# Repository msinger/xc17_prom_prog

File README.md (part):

XC17xxx PROM Programmer
=======================

Tool for programming Xilinx XC17xxx families of PROM chips that are used for storing the configuration
bitstream of the Spartan FPGA.

I developed this programmer to be able to program the PROM chips used in the Wide-Boy64. The Wide-Boy64
CGB uses the XC1701L, and the [Wide-Boy64 AGB](http://iceboy.a-singer.de/doc/wide_boy.html) uses the XC17S20XL.

I originally thought that the Wide-Boy64 CGB uses the XC1701 chip (without the L at the end), because that's
how those chips are labeled on their package. After buying some of those XC1701 chips and reading out their
device ID, I realized that they actually are XC1701L chips. This makes sense by the way, since the Spartan
XC4010XL FPGA inside the Wide-Boy64 CGB has 3.3&nbsp;V IO voltage, which matches the XC1701L PROM. The XC1701
is a 5&nbsp;V device.

You can still buy the XC17S20XL chips here:
- https://de.aliexpress.com/item/1005006854844265.html
- https://www.win-source.net/products/detail/xilinx-inc/xc17s20lpc.html
- https://www.win-source.net/products/detail/xilinx-inc/xc17s20xlpd8c.html

You can still buy a very limited supply of the XC1701L chips here:
- https://www.win-source.net/products/detail/xilinx-inc/xc1701pd8c.html

The Xilinx datasheets recommend the XC17512L to be used with the Spartan XC4010XL (which is the FPGA used in
the Wide-Boy64 CGB). So, the XC17512L could be used instead of the XC1701L.

Files in this repo
------------------

| File/Folder                                 | Description                                                            |
| ------------------------------------------- | ---------------------------------------------------------------------- |
| ./pcb/xc17\_prom\_prog/                     | KiCad project.                                                         |
| ./pcb/xc17\_prom\_prog/bom.ods              | Bill of materials (BOM) needed to populate the PCB.                    |
| ./pcb/lib/                                  | KiCad symbol libraries used in KiCad project.                          |
| ./ftdi/xc17\_prom\_prog\_ftdi\_template.xml | Template for configuring the FTDI chip on the PCB.                     |
| ./hdl/                                      | Verilog project that generates the configuration for the iCE40 FPGA.   |
| ./csharp/                                   | C# project that builds the command line tool for using the programmer. |

List of supported chips
-----------------------

I designed the programmer to be able to program the chips listed in the table below. Those are the ones I was able
to find the "Programmer Qualification Specification" datasheets for. Maybe it can be modified to work for other
variants of those PROM chips when more datasheets are found.

| PROM type              | ID   | Voltage group | Word size (bit) | Density (bit) | N<sub>IDCLK</sub> | N<sub>RSTCLK</sub> | T<sub>PGM</sub> (&micro;s) | T<sub>PGM1</sub> (&micro;s) | T<sub>PRST</sub> (&micro;s) |
| :--------------------- | :--- | :-----------: | --------------: | ------------: | ----------------: | -----------------: | -------------------------: | --------------------------: | --------------------------: |
| XC1736E                | 0xED | A             |              32 |         36288 |              2056 |               2048 |                       1000 |                         N/A |                        5000 |
| XC1765E                | 0xFD | A             |              32 |         65536 |              2056 |               2048 |                       1000 |                         N/A |                        5000 |
| XC1765X aka XC1765EL   | 0xFC | B             |              32 |         65536 |              2056 |               2048 |                       1000 |                         N/A |                        5000 |
| XC17128E               | 0x8D | A             |              64 |        131072 |              4600 |               4104 |                       1000 |                         N/A |                        5000 |
| XC17128X aka XC17128EL | 0x8C | B             |              64 |        131072 |              4600 |               4104 |                       1000 |                         N/A |                        5000 |
| XC17256E               | 0xAD | A             |              64 |        262144 |              4600 |               4104 |                       1000 |                         N/A |                        5000 |
| XC17256X aka XC17256EL | 0xAC | B             |              64 |        262144 |              4600 |               4104 |                       1000 |                         N/A |                        5000 |
| XC17S05                | 0xF8 | A             |              32 |         65536 |              2056 |               2048 |                        100 |                         500 |                        5000 |
| XC17S05XL              | 0x87 | B             |              64 |        131072 |              4600 |               4104 |                        100 |                         500 |                        5000 |
| XC17S10                | 0x88 | A             |              64 |        131072 |              4600 |               4104 |                        100 |                         500 |                        5000 |
| XC17S10XL              | 0x89 | B             |              64 |        131072 |              4600 |               4104 |                        100 |                         500 |                        5000 |
| XC17S20                | 0xA8 | A             |              64 |        262144 |              4600 |               4104 |                        100 |                         500 |                        5000 |
| XC17S20XL              | 0xA9 | B             |              64 |        262144 |              4600 |               4104 |                        100 |                         500 |                        5000 |
| XC17S30                | 0xA6 | A             |              64 |        262144 |              4600 |               4104 |                        100 |                         500 |                        5000 |
| XC17S30XL              | 0xA7 | B             |              64 |        262144 |              4600 |               4104 |                        100 |                         500 |                        5000 |
| XC17S40                | 0x98 | A             |              64 |        524288 |             19791 |              16384 |                        100 |                         500 |                        5000 |
| XC17S40XL              | 0x99 | B             |              64 |        524288 |             19791 |              16384 |                        100 |                         500 |                        5000 |
| XC17S50XL              | 0xD6 | B             |              64 |       1048576 |             19791 |              16384 |                        100 |                         500 |                        5000 |
| XC17S100XL             | 0xD7 | B             |              64 |       1048576 |             19791 |              16384 |                        100 |                         500 |                        5000 |
| XC17S150XL             | 0xD9 | B             |              64 |       1048576 |             19791 |              16384 |                        100 |                         500 |                        5000 |
| XC17512L               | 0x9B | B             |              64 |        524288 |             19791 |              16384 |                        100 |                         500 |                        5000 |
| XC1701                 | 0xDA | A             |              64 |       1048576 |             19791 |              16384 |                        100 |                         500 |                        5000 |
| XC1701L                | 0xDB | B             |              64 |       1048576 |             19791 |              16384 |                        100 |                         500 |                        5000 |
| XC1702L                | 0x3B | C             |              64 |       2097152 |             65632 |              65536 |                        100 |                         200 |                         400 |
| XC1704L                | 0xBB | C             |              64 |       4194304 |             65632 |              65536 |                        100 |                         200 |                         400 |

The table also contains the properties that are different between the PROM types. I listed them here to have an overview;
makes it easier than reading through the datasheets over and over.

The ID column contains the device ID, which has the "density code" in its high nibble and the "algorithm code" in the
low nibble.

N<sub>IDCLK</sub> is the number of times the word address needs to be incremented to reach the manufacturer and device ID
page. N<sub>RSTCLK</sub> is the number of times the word address needs to be incremented to reach the page that stores
the reset polarity.

T<sub>PGM</sub> is the time for how long V<sub>PP1</sub> needs to be applied to program a word. T<sub>PGM1</sub> is the
time that V<sub>PP1</sub> needs to be applied for retries when programming failed. Not all PROM types support alternating
programming and verifying on a word for word basis, so not all of them can do retries. T<sub>PRST</sub> is the time for
how long V<sub>PP1</sub> needs to be applied to program the reset polarity.

The PROMs can be divided into three different "voltage groups", which define what voltages need to be applied to the
VCC and VPP pins:

| Group | V<sub>CC</sub>, V<sub>PP</sub>, V<sub>CCVFY</sub> | V<sub>CCP</sub>, V<sub>CCNOM</sub>, V<sub>PPNOM</sub> | V<sub>PP1</sub> | V<sub>PP2</sub> | V<sub>PPVFY</sub> |
| :---: | ------------------------------------------------: | ----------------------------------------------------: | --------------: | --------------: | ----------------: |
| A     |                                          5&nbsp;V |                                              5&nbsp;V |    12.25&nbsp;V |      5.4&nbsp;V |        5.4&nbsp;V |
| B     |                                        3.3&nbsp;V |                                              5&nbsp;V |    12.25&nbsp;V |      5.4&nbsp;V |        3.7&nbsp;V |
| C     |                                        3.3&nbsp;V |                                            3.3&nbsp;V |    12.25&nbsp;V |      3.7&nbsp;V |        3.7&nbsp;V |

PCB Specification
-----------------

I would recommend using the ZIP file from the latest github release, which contains the Gerber and drill files. Use these
parameters for ordering the PCB:

| Parameter         | Value                      |
| ----------------- | -------------------------- |
| Size              | 123&nbsp;x&nbsp;95&nbsp;mm |
| Layers            | 2                          |
| Min hole size     | 0.3&nbsp;mm                |
| Min track/spacing | 6/6&nbsp;mil               |
| Surface finish    | ENIG                       |

The PCB doesn't contain any vias in pads.

PCB population
--------------

There are two ways to populate the PCB:
* Fully populated, including FPGA and FTDI.
  - Programmer doesn't require any additional hardware.
* Partially populated, leaving out the parts inside the dotted area.
  - Programmer needs to be plugged into an
    [iCE40-HX8K Breakout Board](https://www.latticesemi.com/Products/DevelopmentBoardsAndKits/iCE40HX8KBreakoutBoard.aspx).
  - The HX8K Breakout Board needs to be connected via USB to the PC.
  - The programmer PCB needs power over the USB port, but no data connection.

There are some parts that aren't easy to solder by hand, so if you want to save yourself some trouble, you can get
an HX8K Breakout Board. You don't need a cable to connect the two. Just solder a pin header (J3) at the bottom side
of the programmer PCB, you can plug it directly into the already soldered pin sockets of the HX8K Breakout Board (J2).

IF YOU FULLY POPULATED THE PCB, DO _**NOT**_ CONNECT IT TO AN HX8K BREAKOUT BOARD.

The [BOM](pcb/xc17_prom_prog/bom.ods) contains the parts required to fully populate the PCB. If you plan to only
partially populate it, make sure you don't order the non-required expensive parts like FPGA, FTDI and the LT3030
regulator.

FTDI configuration
------------------

The FTDI chip needs to be configured correctly, otherwise the FPGA can't be programmed. The FTDI configuration is held
in the small EEPROM chip (U4). It is programmed via USB using the FT\_PROG utility that you can download from the
[FTDI website](https://ftdichip.com/utilities/). FT\_PROG requires Windows. It also works from inside a Windows 10 VM
running on VirtualBox.

Program the [template file](ftdi/xc17_prom_prog_ftdi_template.xml) from this repository into the EEPROM. Make sure the
EEPROM is erased first.

Build FPGA bitstream
--------------------

To build the bitstream for the FPGA, you need the following tools:
* [yosys](https://github.com/YosysHQ/yosys)
* [nextpnr](https://github.com/YosysHQ/nextpnr)
* [icestorm](https://github.com/YosysHQ/icestorm)
* Plus all the standard development tools like gnumake, autoconf, automake, m4

On Fedora, you can use the following command line to install everything:

```
dnf install yosys nextpnr icestorm make autoconf automake m4
```

Inside the `hdl` directory of the repository, run the following commands to build the bitstream for a fully populated
PCB:

```
autoreconf -i
./configure --enable-board=xc17_prom_prog
make
```

If you've partially populated the PCB and connected it to the HX8K Breakout Board, then use the following commands
instead:

```
autoreconf -i
./configure --enable-board=hx8k_brk
make
```

Program FPGA bitstream into Flash
---------------------------------

The FPGA bitstream needs to be programmed into the flash chip on the PCB or HX8K Breakout Board via USB.

On a fully populated PCB, make sure to put the J1 jumpers into the "Program Flash" configuration, which is
horizontal, like it is indicated on the PCB silk print. JP1 has to be bridged as well. If you want to flash the HX8K
Breakout Board, read the documentation for that. Once the jumpers are placed correctly, you don't have to fiddle
with them anymore. Other jumper configurations are only for development, when you want to test a new FPGA
configuration without burning it into the flash. So you could also bridge the jumpers directly with solder or small
wires on the PCB.

If you've built the FPGA bitstream yourself, you can run the following command inside the `hdl` directory to program
the bitstream:

```
make prog
```

If you want to program a prebuilt release that you've downloaded from github, use the following command:

```
iceprog xc17_prom_prog.bin
```

I haven't tried it, but it should also be possible to use the
[Lattice iCEcube2 Software](https://www.latticesemi.com/en/Products/DesignSoftwareAndIP/FPGAandLDS/iCEcube2)
to program either the `asc` file or the `bin` file.

The green LED D2 (labeled CDONE) indicates that the FPGA has successfully loaded the configuration from the
flash into its configuration RAM. So, on a fully populated PCB, this LED should switch on after the flash was
programmed correctly, every time you power up the board (with the correct jumper configuration described above).
The HX8K Breakout Board also has such an LED (D10) near the jumpers.

Build the command line tool
---------------------------

For building the C# command line tool on Linux, you need the Mono framework and the standard tools gnumake, autoconf,
automake and m4.

For building it on Windows, you need the .NET Framework and some POSIX-like environment for building: Either Cygwin or
Msys2. Gnumake, autoconf, automake and m4 need to be installed in that environment. The C# compiler executable (csc.exe)
must also be callable in your build environment. Make sure it is in `$PATH`.

Run the following commands inside the `csharp` directory of the repository to build the command line tool:

```
autoreconf -i
./configure
make
```

If you want, you can install it with `make install`.

Calibration and testing of PCB
------------------------------

After populating the PCB you have to calibrate all the voltages using the trim potentiometers at the top. Just
hold your voltage meter at the test points near the potentiometers. The target voltage that each test point should
have is labeled on the silk screen print.

If the LDOs are not providing high enough voltages, check if the step-up converters provide roughly 15&nbsp;V and
8.5&nbsp;V at test points TP12 and TP13. The 15&nbsp;V is used by the first LDO (U6) to generate the 12.25&nbsp;V.
The other six LDOs use the 8.5&nbsp;V to generate their lower voltages. In case you are wondering, the reason why
there are two 3.3&nbsp;V LDOs and two 5&nbsp;V LDOs is this: One of each is there for providing the VCC voltage for
the PROM, the other one (of each) is there for providing the VPP voltage. We can't use the same LDOs for VCC and
VPP, because VPP will be switched to 12.25&nbsp;V for issuing the programming pulses. There is a short moment during
switching where the 12.25&nbsp;V and the lower voltage (3.3&nbsp;V or 5&nbsp;V) will both be connected to VPP at the
same time. At this moment, the 12.25&nbsp;V will back flow to the other LDO. If we'd use the same LDO, then the
12.25&nbsp;V would also reach the VCC pin of the PROM, which is not good. VCC needs to be constant at all time, and
it can't handle 12&nbsp;V. Only VPP can switch around.

Before trying to read or program an actual PROM chip, you first should do some tests to make sure the PCB is
working correctly.

Connect the PCB via USB and run the command line tool with the following options:

```
xc17_prom_prog.exe COMMPORT --test-echo
```

Replace *`COMMPORT`* with the correct serial port. On Windows this would be `COM2:` or something. On Linux it is
something like `/dev/ttyUSB1`. The FTDI chip has two serial ports. Usually, the first one is the one that is used
for programming the flash chip (U1) that holds the FPGA bitstream. The second port is the one we need most likely,
so try this one first. Of course, on Linux you have to call the command with `mono`, like this:

```
mono xc17_prom_prog.exe /dev/ttyUSB1 --test-echo
```

`--test-echo` just tests the serial communication and the BRAM inside the FPGA.

Next, we can test the voltage switching MOSFETs:

```
xc17_prom_prog.exe COMMPORT --test-voltage VOLTAGE
```

Again, replace *`COMMPORT`* with the actual port. For *`VOLTAGE`* insert one of the following:

 - `vcc-3v3`
 - `vcc-5v`
 - `vpp-3v3`
 - `vpp-3v7`
 - `vpp-5v`
 - `vpp-5v4`
 - `vpp-12v25`
 - `off`

For example, `vcc-3v3` will switch 3.3&nbsp;V onto the VCC pin of the PROM. (Don't actually put a PROM chip
into the socket when testing the voltages, please!) You can measure that with your voltage meter at test point
TP19. `vpp-5v4` will switch 5.4&nbsp;V onto the VPP pin at test point TP18, and so on. This test option only
enables one single voltage at a time, so don't worry, you can't make short circuits. `off` switches all MOSFETs
off, as the name implies. The red LED (D20) signals whenever at least one of the two pins (VCC, VPP) is powered
to indicate that you shouldn't insert or remove the chip right now.

There are actually three other options that can be inserted for *`VOLTAGE`* (`vcc-gnd`, `vpp-gnd` and
`vpp-gnd-weak`), but you can't measure anything there, because they are pulling the respective pin to ground.

If the voltage switching works, we should test if the 12.25&nbsp;V pulse looks okay using an oscilloscope. Hook
up one probe to test point TP18 (VPP<sub>PROM</sub>) and one to TP19 (VCC<sub>PROM</sub>). Configure the trigger
to around ~8&nbsp;V on the probe connected to VPP<sub>PROM</sub>, so we can trigger when VPP raises from
5&nbsp;V to 12.25&nbsp;V. Then run this command:

```
xc17_prom_prog.exe COMMPORT --prom xc17s20xl --detect
```

`--prom xc17s20xl` configures the programmer to use the voltages required by the XC17S20XL PROM chip (which is
used in the Wide-Boy64 AGB). This PROM chip is a 3.3&nbsp;V device, but it needs to be powered with 5&nbsp;V
to enter "programming mode". `--detect` makes the programmer just read the manufacturer and device IDs of the
PROM chip, without reading or programming anything else. For reading the IDs, the PROM has to enter "programming
mode", which sounds counterintuitive, but that's how it's done. So, the programmer will switch VCC and VPP to
5&nbsp;V. Then shortly after switching them to 5&nbsp;V, it will issue a short pulse of 12.25&nbsp;V on VPP.

On the oscilloscope we want to check the following things:

 * There should be no over and/or under shooting when the voltage on VPP raises from 5&nbsp;V to 12.25&nbsp;V
   and falls back down to 5&nbsp;V.
 * The raising and falling of the voltage on VPP shouldn't take much longer than 5&nbsp;&micro;s.
 * According to the datasheets, VCC must stay stable within &plusmn;50&nbsp;mV. I wasn't able to comply with
   that. My VCC was always swinging a bit more when the 12.25&nbsp;V ramps up on VPP. I couldn't figure out
   why this happens and how to fix it. Just make sure VCC looks reasonable, programming the PROM will work
   anyway.

If VPP takes too long to fall down to 5&nbsp;V, then the resistor R82 is probably too big and you should try
a smaller one. If VPP drops below 5&nbsp;V or if it is unstable or oscillating for some microseconds after
falling down, then resistor R82 could be too small. Try a bigger one in that case.

This picture shows VCC (yellow) and VPP (cyan) during the 12.25&nbsp;V pulse. The dark blue and purple channels
are added, so I can correctly photoshop the additional signals from the logic analyzer underneath the
oscilloscope screenshot. You can see VCC getting a bit unstable while VPP rises to 12.25&nbsp;V. There is a
delay of 4&nbsp;&micro;s between switching off the 5&nbsp;V LDO and switching on the 12.25&nbsp;V LDO for VPP.
This delay is needed, because when switching off, it takes 2 or 3&nbsp;&micro;s until the gates of the MOSFETs
get drained and the MOSFETs actually switch off. I had chosen a slightly longer delay to make sure that the
5 and 12.25&nbsp;V LDOs are not switched on at the same time, because this would allow the 12.25&nbsp;V to
backflow through the diode (D5) above the 5&nbsp;V LDO. This would destabilize both voltages and takes a long
time for VPP to climb up to 12.25&nbsp;V due to the near short circuit through the diode. The same
4&nbsp;&micro;s pause exists at the end of the pulse, where the 12.25&nbsp;V gets drained by switching on the
VPP\_GND and VPP\_GND\_WEAK signals. VPP\_GND switches on the NPN transistor Q20 to quickly drain VPP down
towards GND. VPP\_GND\_WEAK switches on Q21 to drain VPP through resistor R82. VPP\_GND is only enabled for
2&nbsp;&micro;s. We don't want to drain VPP lower than 5&nbsp;V. We could leave it enabled for longer, but
I want to stay on the safe side, we need to consider tolerances of the BC850 transistors. VPP\_GND\_WEAK is
enabled for 7&nbsp;&micro;s and VPP\_5V (which enables the 5&nbsp;V LDO) overlaps with it for 2&nbsp;&micro;s.
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
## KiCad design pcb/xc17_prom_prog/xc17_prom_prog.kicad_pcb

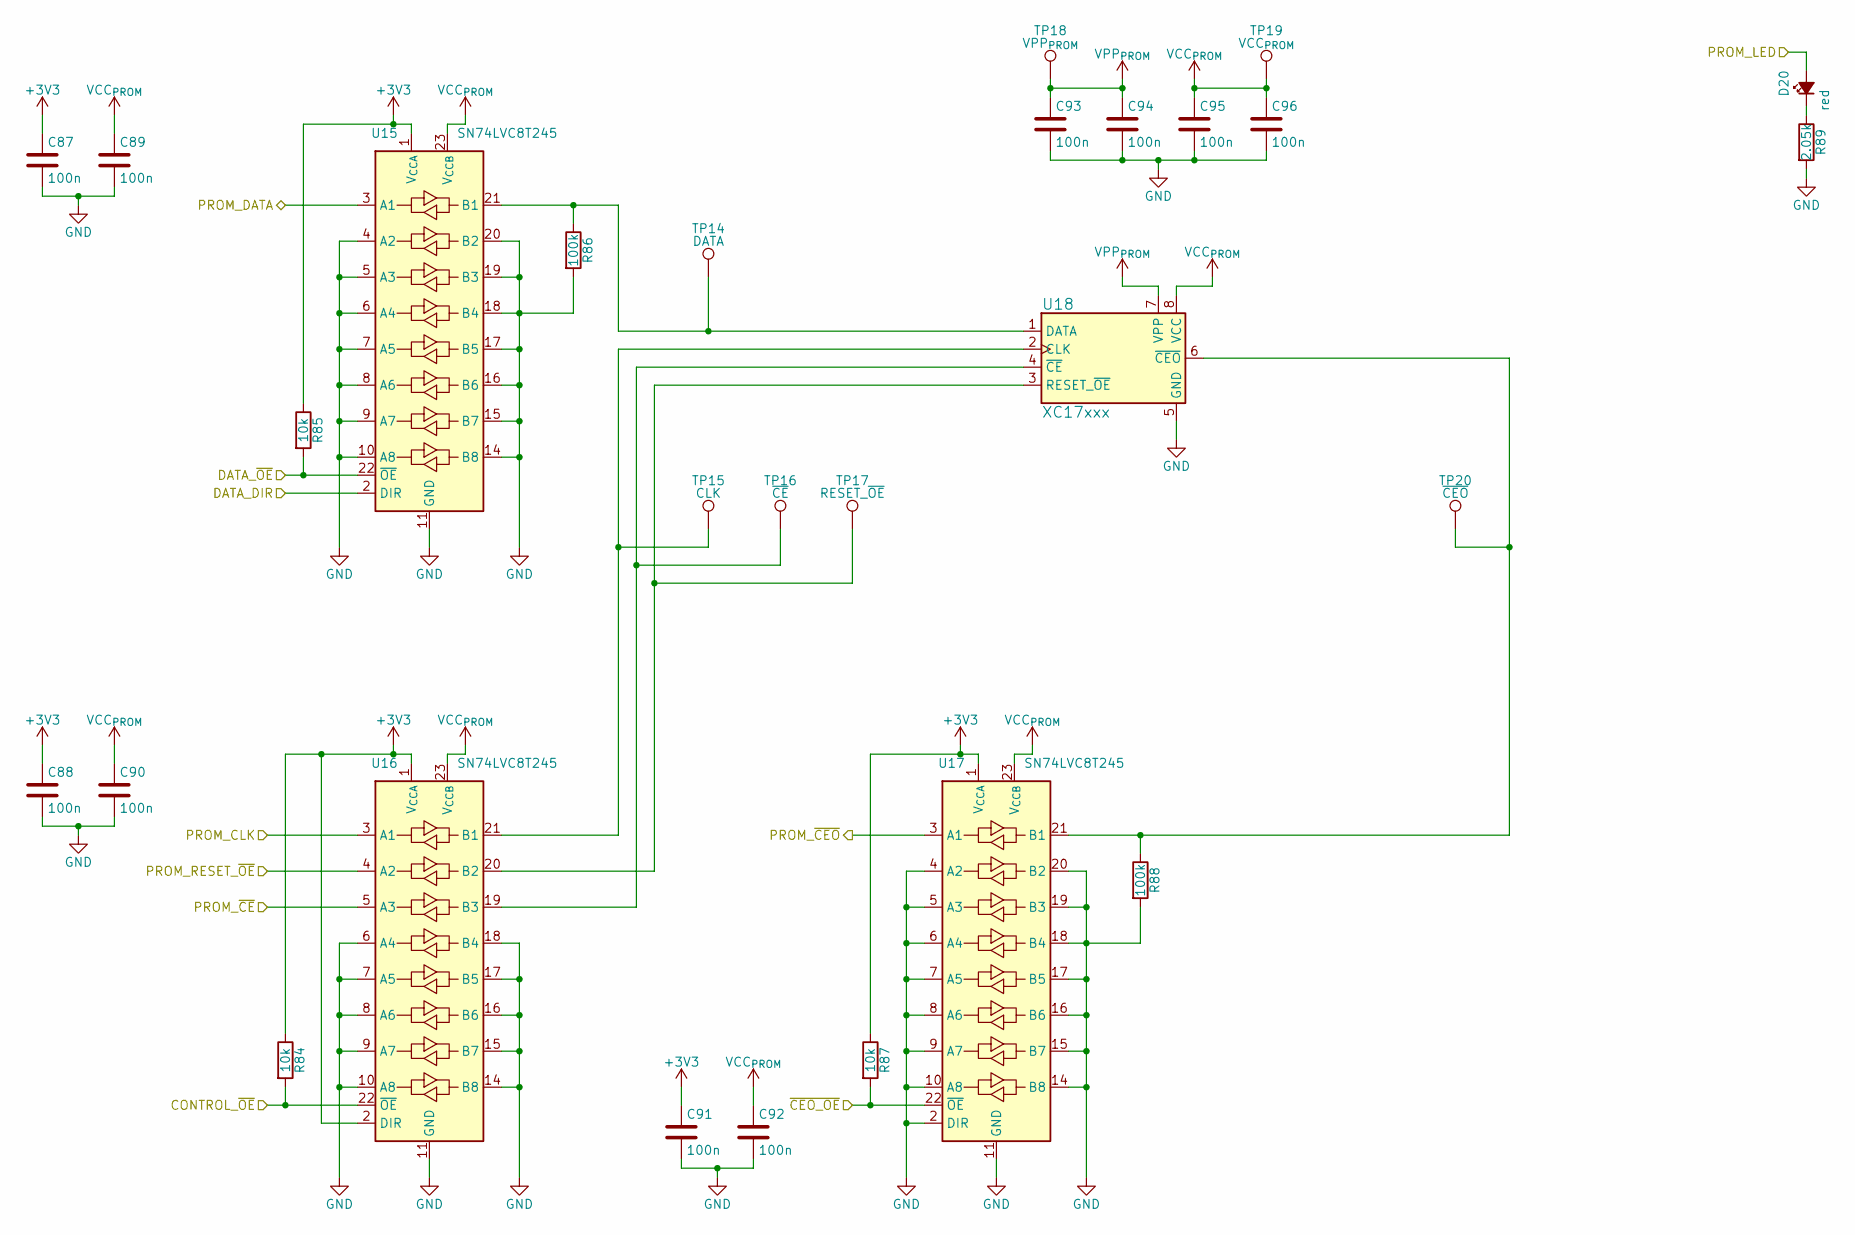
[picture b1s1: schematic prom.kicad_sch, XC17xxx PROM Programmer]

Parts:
C87, C88, C89, C90, C91, C92, C93, C94, C95, C96: 100n; C_0603_1608Metric
D20: red; LED_0805_2012Metric
R84, R85, R87: 10k; R_0603_1608Metric
R86, R88: 100k; R_0603_1608Metric
R89: 2.05k; R_0603_1608Metric
TP14: DATA; TestPoint_Keystone_5010-5014_Multipurpose
TP15: CLK; TestPoint_Keystone_5010-5014_Multipurpose
TP16: ~{CE}; TestPoint_Keystone_5010-5014_Multipurpose
TP17: RESET_~{OE}; TestPoint_Keystone_5010-5014_Multipurpose
TP18: VPP_{PROM}; TestPoint_Keystone_5010-5014_Multipurpose
TP19: VCC_{PROM}; TestPoint_Keystone_5010-5014_Multipurpose
TP20: ~{CEO}; TestPoint_Keystone_5010-5014_Multipurpose
U15, U16, U17: SN74LVC8T245; TSSOP-24_4.4x7.8mm_P0.65mm
U18: XC17xxx; DIP-8_W7.62mm_Socket

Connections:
+3V3: C87.1, C88.1, C91.1, R84.1, R85.1, R87.1, U15.1 (V_{CCA}), U16.1 (V_{CCA}), U16.2 (DIR), U17.1 (V_{CCA}); also elsewhere on the board
/FPGA/CONTROL_~OE: R84.2, U16.22 (~OE); also elsewhere on the board
/FPGA/DATA_DIR: U15.2 (DIR); also elsewhere on the board
/FPGA/DATA_~OE: R85.2, U15.22 (~OE); also elsewhere on the board
/FPGA/PROM_CLK: U16.3 (A1); also elsewhere on the board
/FPGA/PROM_DATA: U15.3 (A1); also elsewhere on the board
/FPGA/PROM_LED: D20.2 (A); also elsewhere on the board
/FPGA/PROM_RESET_~OE: U16.4 (A2); also elsewhere on the board
/FPGA/PROM_~CEO: U17.3 (A1); also elsewhere on the board
/FPGA/PROM_~CE: U16.5 (A3); also elsewhere on the board
/FPGA/~CEO_OE: R87.2, U17.22 (~OE); also elsewhere on the board
GND: C87.2, C88.2, C89.2, C90.2, C91.2, C92.2, C93.2, C94.2, C95.2, C96.2, R86.2, R88.2, R89.2, U15.4 (A2), U15.5 (A3), U15.6 (A4), U15.7 (A5), U15.8 (A6), U15.9 (A7), U15.10 (A8), U15.11 (GND), U15.12 (GND), U15.13 (GND), U15.14 (B8), U15.15 (B7), U15.16 (B6), U15.17 (B5), U15.18 (B4), U15.19 (B3), U15.20 (B2), U16.6 (A4), U16.7 (A5), U16.8 (A6), U16.9 (A7), U16.10 (A8), U16.11 (GND), U16.12 (GND), U16.13 (GND), U16.14 (B8), U16.15 (B7), U16.16 (B6), U16.17 (B5), U16.18 (B4), U17.2 (DIR), U17.4 (A2), U17.5 (A3), U17.6 (A4), U17.7 (A5), U17.8 (A6), U17.9 (A7), U17.10 (A8), U17.11 (GND), U17.12 (GND), U17.13 (GND), U17.14 (B8), U17.15 (B7), U17.16 (B6), U17.17 (B5), U17.18 (B4), U17.19 (B3), U17.20 (B2), U18.5 (GND); also elsewhere on the board
unnamed: D20.1 (K), R89.1
unnamed: R86.1, TP14.1, U15.21 (B1), U18.1 (DATA)
unnamed: TP15.1, U16.21 (B1), U18.2 (CLK)
unnamed: TP17.1, U16.20 (B2), U18.3 (RESET_~OE)
unnamed: TP16.1, U16.19 (B3), U18.4 (~CE)
unnamed: R88.1, TP20.1, U17.21 (B1), U18.6 (~CEO)
VCC_{PROM}: C89.1, C90.1, C92.1, C95.1, C96.1, TP19.1, U15.23 (V_{CCB}), U15.24 (V_{CCB}), U16.23 (V_{CCB}), U16.24 (V_{CCB}), U17.23 (V_{CCB}), U17.24 (V_{CCB}), U18.8 (VCC); also elsewhere on the board
VPP_{PROM}: C93.1, C94.1, TP18.1, U18.7 (VPP); also elsewhere on the board

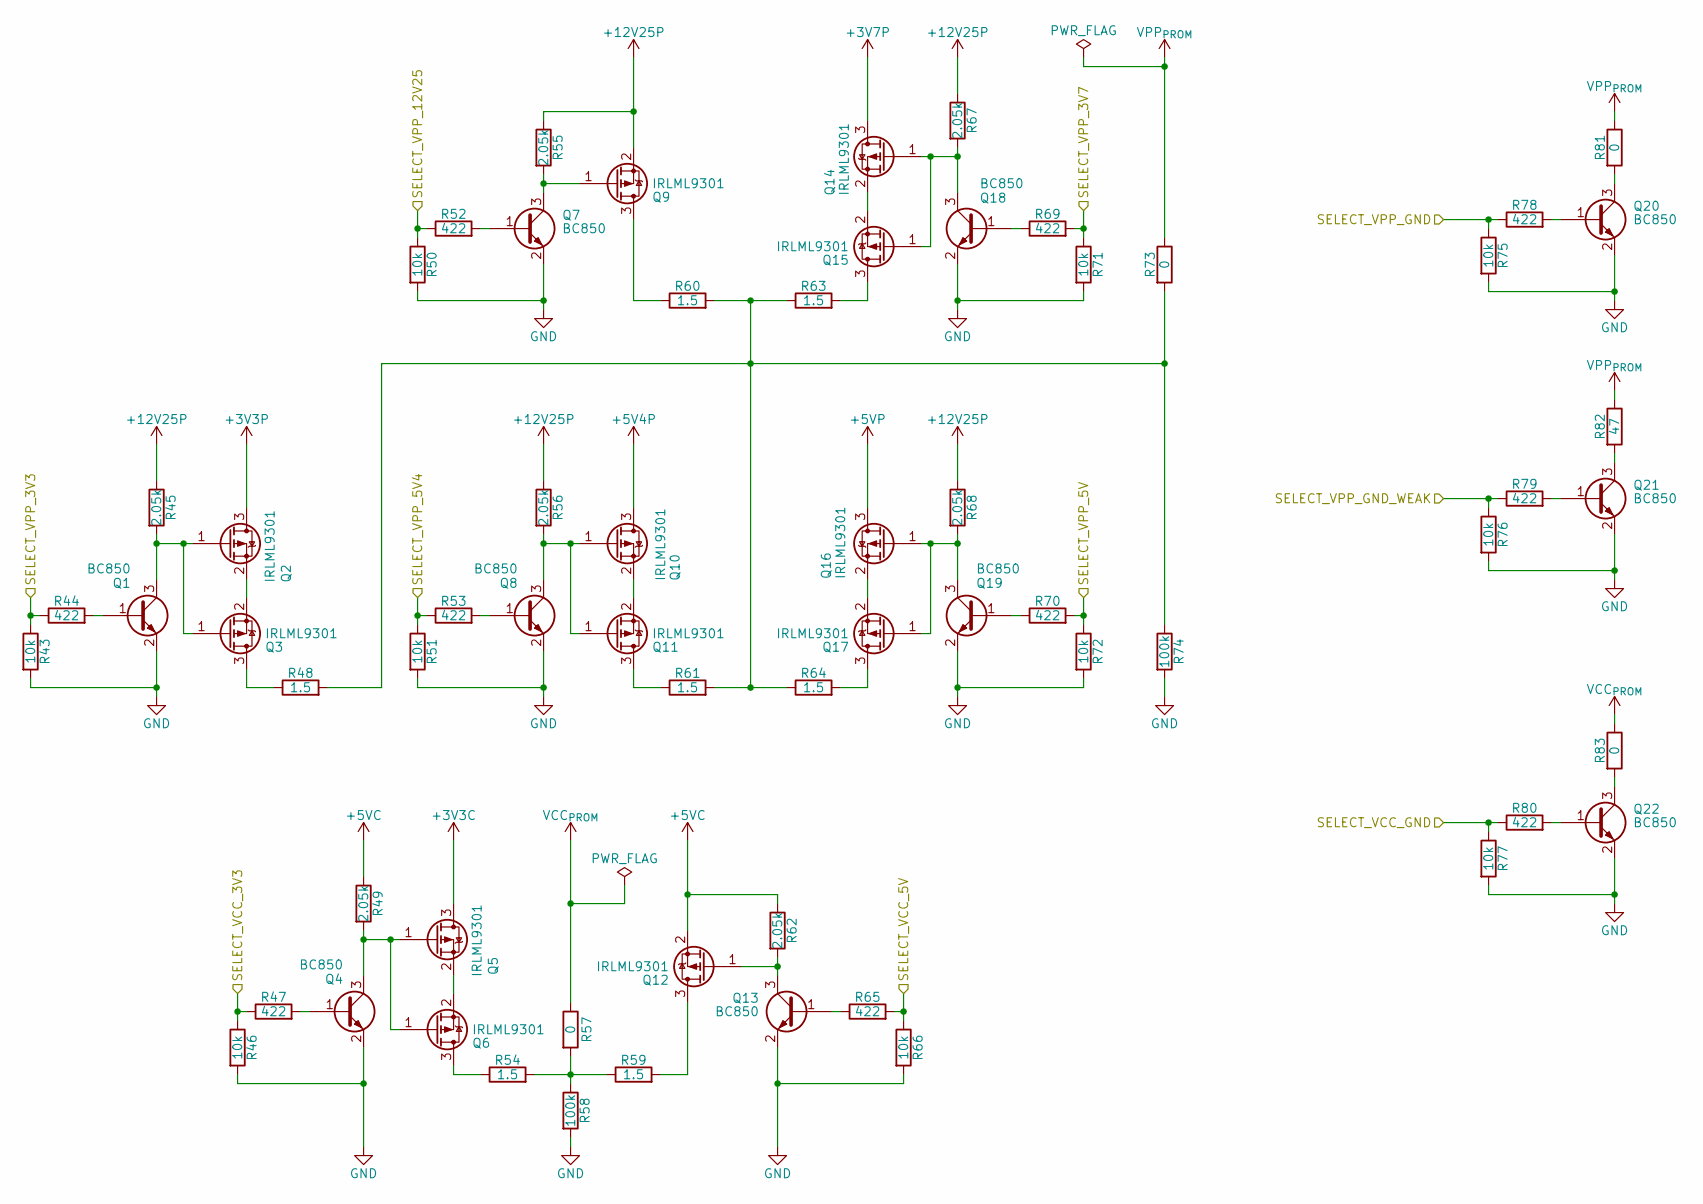
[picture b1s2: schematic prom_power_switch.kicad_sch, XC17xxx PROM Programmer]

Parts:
Q1, Q4, Q7, Q8, Q13, Q18, Q19, Q20, Q21, Q22: BC850; SOT-23
Q2, Q3, Q5, Q6, Q9, Q10, Q11, Q12, Q14, Q15, Q16, Q17: IRLML9301; SOT-23
R43, R46, R50, R51, R66, R71, R72, R75, R76, R77: 10k; R_0603_1608Metric
R44, R47, R52, R53, R65, R69, R70, R78, R79, R80: 422; R_0603_1608Metric
R45, R49, R55, R56, R62, R67, R68: 2.05k; R_0603_1608Metric
R48, R54, R59, R60, R61, R63, R64: 1.5; R_0603_1608Metric
R57, R73, R81, R83: 0; R_0603_1608Metric
R58, R74: 100k; R_0603_1608Metric
R82: 47; R_0603_1608Metric

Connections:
+3V3C: Q5.3 (D); also elsewhere on the board
+3V3P: Q2.3 (D); also elsewhere on the board
+3V7P: Q14.3 (D); also elsewhere on the board
+5V4P: Q10.3 (D); also elsewhere on the board
+5VC: Q12.2 (S), R49.1, R62.1; also elsewhere on the board
+5VP: Q16.3 (D); also elsewhere on the board
+12V25P: Q9.2 (S), R45.1, R55.1, R56.1, R67.1, R68.1; also elsewhere on the board
/FPGA/SELECT_VCC_3V3: R46.1, R47.1; also elsewhere on the board
/FPGA/SELECT_VCC_5V: R65.2, R66.1; also elsewhere on the board
/FPGA/SELECT_VCC_GND: R77.1, R80.1; also elsewhere on the board
/FPGA/SELECT_VPP_3V3: R43.1, R44.1; also elsewhere on the board
/FPGA/SELECT_VPP_3V7: R69.2, R71.1; also elsewhere on the board
/FPGA/SELECT_VPP_5V: R70.2, R72.1; also elsewhere on the board
/FPGA/SELECT_VPP_5V4: R51.1, R53.1; also elsewhere on the board
/FPGA/SELECT_VPP_12V25: R50.1, R52.1; also elsewhere on the board
/FPGA/SELECT_VPP_GND: R75.1, R78.1; also elsewhere on the board
/FPGA/SELECT_VPP_GND_WEAK: R76.1, R79.1; also elsewhere on the board
GND: Q1.2 (E), Q4.2 (E), Q7.2 (E), Q8.2 (E), Q13.2 (E), Q18.2 (E), Q19.2 (E), Q20.2 (E), Q21.2 (E), Q22.2 (E), R43.2, R46.2, R50.2, R51.2, R58.2, R66.2, R71.2, R72.2, R74.2, R75.2, R76.2, R77.2; also elsewhere on the board
unnamed: Q1.1 (B), R44.2
unnamed: Q1.3 (C), Q2.1 (G), Q3.1 (G), R45.2
unnamed: Q2.2 (S), Q3.2 (S)
unnamed: Q3.3 (D), R48.1
unnamed: Q4.1 (B), R47.2
unnamed: Q4.3 (C), Q5.1 (G), Q6.1 (G), R49.2
unnamed: Q5.2 (S), Q6.2 (S)
unnamed: Q6.3 (D), R54.1
unnamed: Q7.1 (B), R52.2
unnamed: Q7.3 (C), Q9.1 (G), R55.2
unnamed: Q8.1 (B), R53.2
unnamed: Q9.3 (D), R60.1
unnamed: Q8.3 (C), Q10.1 (G), Q11.1 (G), R56.2
unnamed: Q10.2 (S), Q11.2 (S)
unnamed: Q11.3 (D), R61.1
unnamed: Q12.3 (D), R59.2
unnamed: Q12.1 (G), Q13.3 (C), R62.2
unnamed: Q13.1 (B), R65.1
unnamed: Q14.1 (G), Q15.1 (G), Q18.3 (C), R67.2
unnamed: Q14.2 (S), Q15.2 (S)
unnamed: Q15.3 (D), R63.2
unnamed: Q16.1 (G), Q17.1 (G), Q19.3 (C), R68.2
unnamed: Q16.2 (S), Q17.2 (S)
unnamed: Q17.3 (D), R64.2
unnamed: Q18.1 (B), R69.1
unnamed: Q19.1 (B), R70.1
unnamed: Q20.1 (B), R78.2
unnamed: Q20.3 (C), R81.2
unnamed: Q21.1 (B), R79.2
unnamed: Q21.3 (C), R82.2
unnamed: Q22.1 (B), R80.2
unnamed: Q22.3 (C), R83.2
unnamed: R48.2, R60.2, R61.2, R63.1, R64.1, R73.2, R74.1
unnamed: R54.2, R57.2, R58.1, R59.1
VCC_{PROM}: R57.1, R83.1; also elsewhere on the board
VPP_{PROM}: R73.1, R81.1, R82.1; also elsewhere on the board

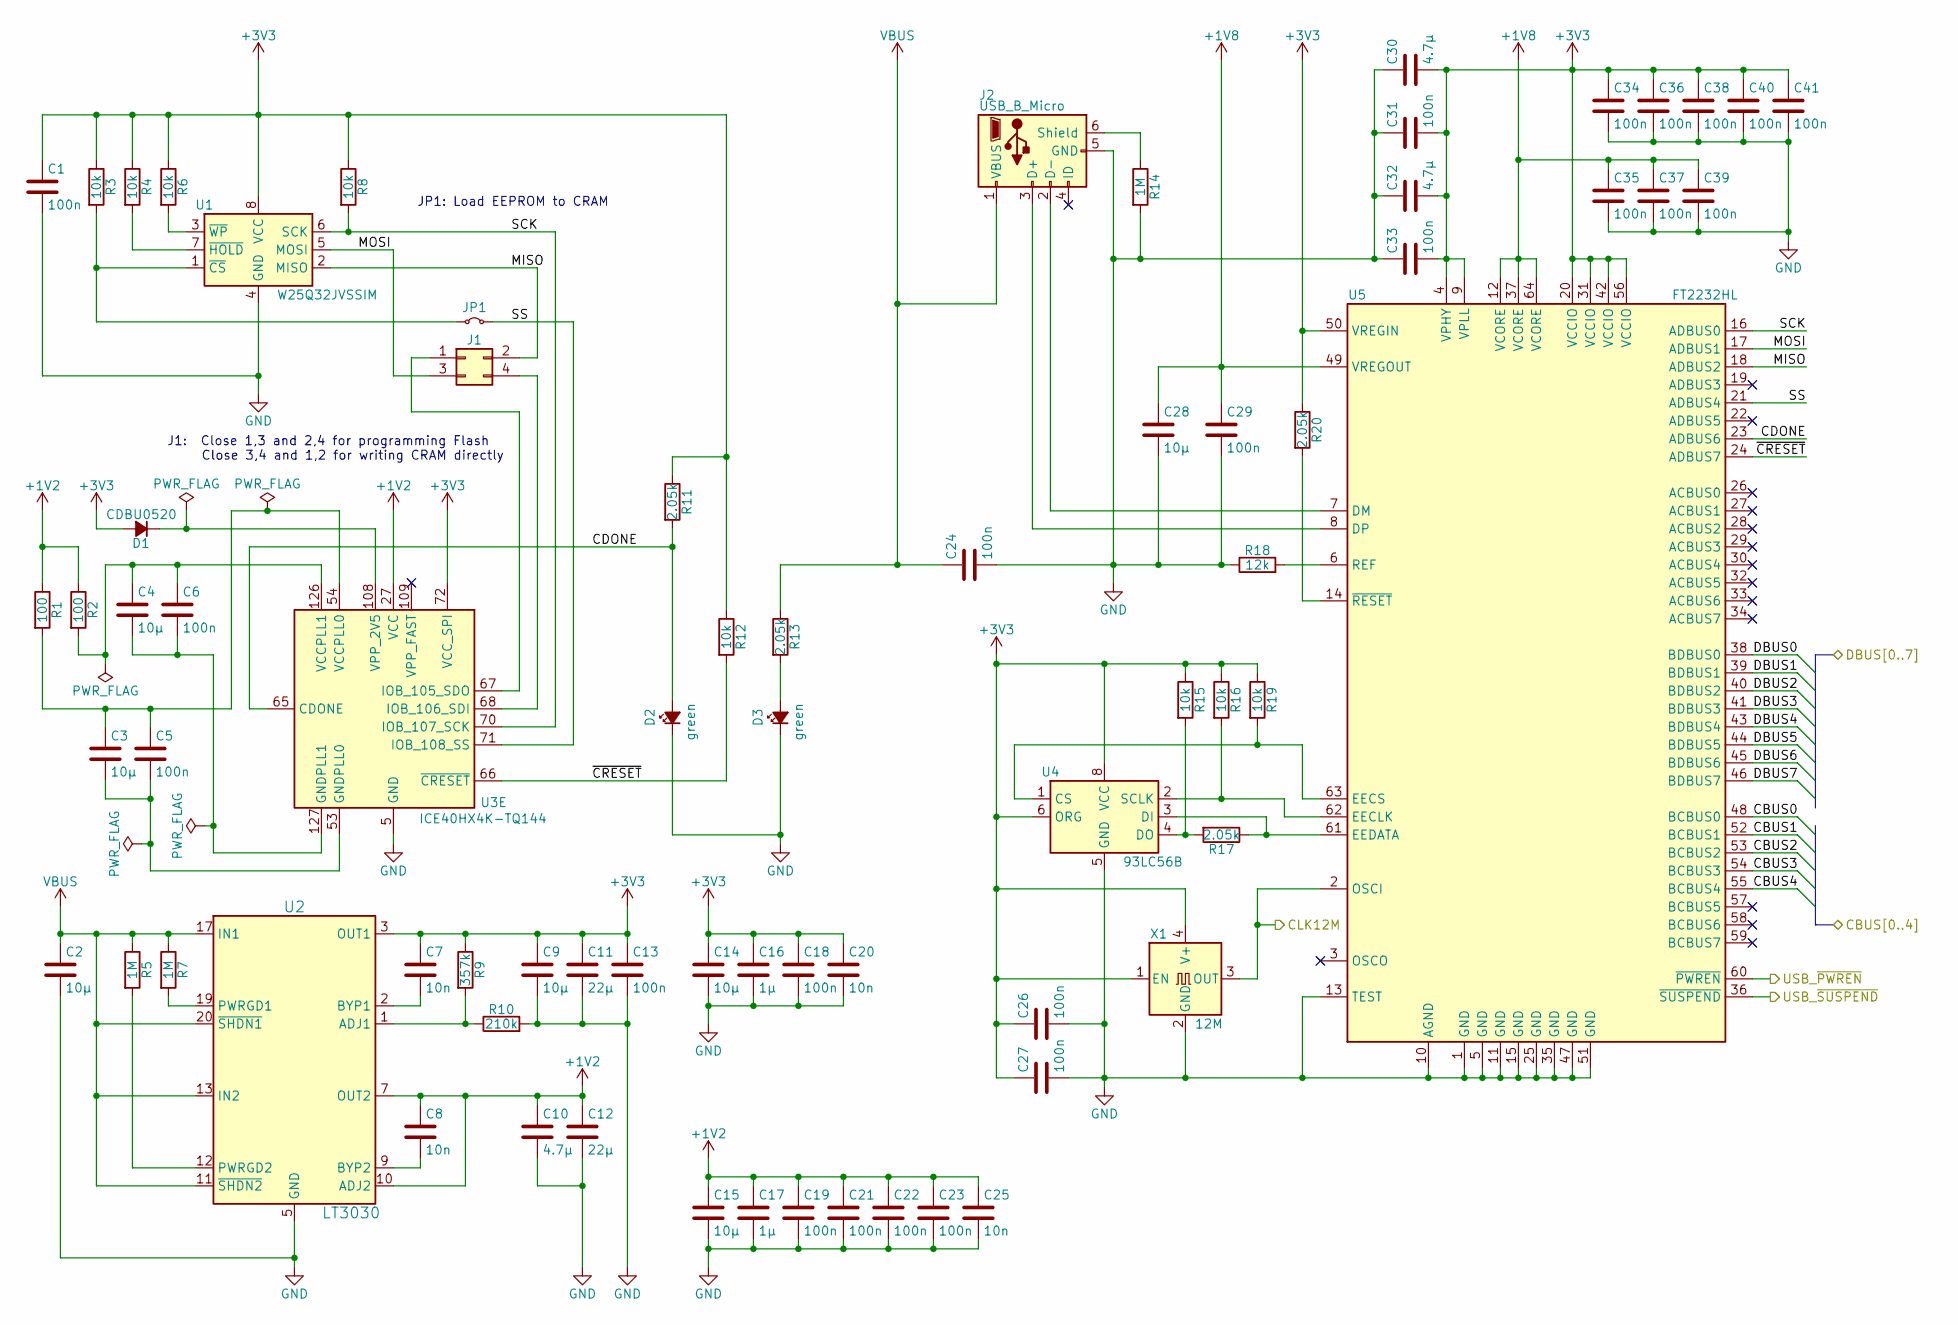
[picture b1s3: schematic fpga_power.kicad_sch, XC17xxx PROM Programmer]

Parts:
C1, C5, C6, C13, C18, C19, C21, C22, C23, C24, C26, C27, C29, C31, C33, C34, C35, C36, C37, C38, C39, C40, C41: 100n; C_0603_1608Metric
C2, C3, C4, C9, C14, C15, C28: 10µ; C_0603_1608Metric
C7, C8, C20, C25: 10n; C_0603_1608Metric
C10, C30, C32: 4.7µ; C_0603_1608Metric
C11, C12: 22µ; C_0805_2012Metric
C16, C17: 1µ; C_0603_1608Metric
D1: CDBU0520; D_0603_1608Metric
D2, D3: green; LED_0805_2012Metric
J1: Conn_02x02_Odd_Even; PinHeader_2x02_P2.54mm_Vertical
J2: USB_B_Micro; USB_Micro-B_Molex-105017-0001
JP1: Jumper_2_Small_Bridged; TestPoint_2Pads_Pitch2.54mm_Drill0.8mm
R1, R2: 100; R_0603_1608Metric
R3, R4, R6, R8, R12, R15, R16, R19: 10k; R_0603_1608Metric
R5, R7, R14: 1M; R_0603_1608Metric
R9: 357k; R_0603_1608Metric
R10: 210k; R_0603_1608Metric
R11, R13, R17, R20: 2.05k; R_0603_1608Metric
R18: 12k; R_0603_1608Metric
U1: W25Q32JVSSIM; SOIC-8W_5.3x5.3mm_P1.27mm
U2: LT3030; ETSSOP-20-1EP_4.4x6.5mm_P0.65mm_EP3x4.2mm
U3: ICE40HX4K-TQ144; TQFP-144_20x20mm_P0.5mm
U4: 93LC56B; SOIC-8_3.9x4.9mm_P1.27mm
U5: FT2232HL; LQFP-64_10x10mm_P0.5mm
X1: 12M; Oscillator_SMD_EuroQuartz_XO32-4Pin_3.2x2.5mm

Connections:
+1V2: C8.1, C10.1, C12.1, C15.1, C17.1, C19.1, C21.1, C22.1, C23.1, C25.1, R1.1, R2.1, U2.7 (OUT2), U2.8 (OUT2), U2.10 (ADJ2), U3.27 (VCC), U3.40 (VCC), U3.92 (VCC), U3.111 (VCC)
+1V8: C28.1, C29.1, C35.1, C37.1, C39.1, U5.12 (VCORE), U5.37 (VCORE), U5.49 (VREGOUT), U5.64 (VCORE)
+3V3: C1.1, C7.1, C9.1, C11.1, C13.1, C14.1, C16.1, C18.1, C20.1, C26.1, C27.1, C30.2, C31.2, C32.2, C33.2, C34.1, C36.1, C38.1, C40.1, C41.1, D1.2 (A), R3.1, R4.1, R6.1, R8.1, R9.1, R11.1, R12.1, R15.1, R16.1, R19.1, R20.1, U1.8 (VCC), U2.3 (OUT1), U2.4 (OUT1), U3.72 (VCC_SPI), U4.6 (ORG), U4.8 (VCC), U5.4 (VPHY), U5.9 (VPLL), U5.20 (VCCIO), U5.31 (VCCIO), U5.42 (VCCIO), U5.50 (VREGIN), U5.56 (VCCIO), X1.1 (EN), X1.4 (V+); also elsewhere on the board
/FPGA Power/CBUS0: U5.48 (BCBUS0); also elsewhere on the board
/FPGA Power/CBUS1: U5.52 (BCBUS1); also elsewhere on the board
/FPGA Power/CBUS2: U5.53 (BCBUS2); also elsewhere on the board
/FPGA Power/CBUS3: U5.54 (BCBUS3); also elsewhere on the board
/FPGA Power/CBUS4: U5.55 (BCBUS4); also elsewhere on the board
/FPGA Power/CDONE: D2.2 (A), R11.2, U3.65 (CDONE), U5.23 (ADBUS6)
/FPGA Power/DBUS0: U5.38 (BDBUS0); also elsewhere on the board
/FPGA Power/DBUS1: U5.39 (BDBUS1); also elsewhere on the board
/FPGA Power/DBUS2: U5.40 (BDBUS2); also elsewhere on the board
/FPGA Power/DBUS3: U5.41 (BDBUS3); also elsewhere on the board
/FPGA Power/DBUS4: U5.43 (BDBUS4); also elsewhere on the board
/FPGA Power/DBUS5: U5.44 (BDBUS5); also elsewhere on the board
/FPGA Power/DBUS6: U5.45 (BDBUS6); also elsewhere on the board
/FPGA Power/DBUS7: U5.46 (BDBUS7); also elsewhere on the board
/FPGA Power/MISO: J1.2, U1.2 (MISO), U5.18 (ADBUS2)
/FPGA Power/MOSI: J1.3, U1.5 (MOSI), U5.17 (ADBUS1)
/FPGA Power/SCK: R8.2, U1.6 (SCK), U3.70 (IOB_107_SCK), U5.16 (ADBUS0)
/FPGA Power/SS: JP1.2 (B), U3.71 (IOB_108_SS), U5.21 (ADBUS4)
/FPGA Power/USB_~PWREN: U5.60 (~PWREN); also elsewhere on the board
/FPGA Power/USB_~SUSPEND: U5.36 (~SUSPEND); also elsewhere on the board
/FPGA Power/~CRESET: R12.2, U3.66 (~CRESET), U5.24 (ADBUS7)
/FPGA/CLK12M: U5.2 (OSCI), X1.3 (OUT); also elsewhere on the board
GND: C1.2, C2.2, C9.2, C10.2, C11.2, C12.2, C13.2, C14.2, C15.2, C16.2, C17.2, C18.2, C19.2, C20.2, C21.2, C22.2, C23.2, C24.2, C25.2, C26.2, C27.2, C28.2, C29.2, C30.1, C31.1, C32.1, C33.1, C34.2, C35.2, C36.2, C37.2, C38.2, C39.2, C40.2, C41.2, D2.1 (K), D3.1 (K), J2.5 (GND), R10.2, R14.2, R18.1, U1.4 (GND), U2.5 (GND), U2.6 (GND), U2.15 (GND), U2.16 (GND), U2.21 (GND), U3.5 (GND), U3.13 (GND), U3.14 (GND), U3.59 (GND), U3.69 (GND), U3.86 (GND), U3.103 (GND), U3.132 (GND), U3.140 (GND), U4.5 (GND), U5.1 (GND), U5.5 (GND), U5.10 (AGND), U5.11 (GND), U5.13 (TEST), U5.15 (GND), U5.25 (GND), U5.35 (GND), U5.47 (GND), U5.51 (GND), X1.2 (GND); also elsewhere on the board
unnamed: D1.1 (K), U3.108 (VPP_2V5)
unnamed: D3.2 (A), R13.2
unnamed: J1.1, U3.67 (IOB_105_SDO)
unnamed: J1.4, U3.68 (IOB_106_SDI)
unnamed: J2.3 (D+), U5.8 (DP)
unnamed: J2.2 (D-), U5.7 (DM)
unnamed: J2.6 (Shield), R14.1
unnamed: JP1.1 (A), R3.2, U1.1 (~CS)
unnamed: R4.2, U1.7 (~HOLD)
unnamed: R6.2, U1.3 (~WP)
unnamed: R9.2, R10.1, U2.1 (ADJ1)
unnamed: C7.2, U2.2 (BYP1)
unnamed: C8.2, U2.9 (BYP2)
unnamed: R7.2, U2.19 (PWRGD1)
unnamed: R5.2, U2.12 (PWRGD2)
unnamed: C3.2, C5.2, U3.53 (GNDPLL0)
unnamed: C4.2, C6.2, U3.127 (GNDPLL1)
unnamed: C3.1, C5.1, R1.2, U3.54 (VCCPLL0)
unnamed: C4.1, C6.1, R2.2, U3.126 (VCCPLL1)
unnamed: R19.2, U4.1 (CS), U5.63 (EECS)
unnamed: R17.1, U4.3 (DI), U5.61 (EEDATA)
unnamed: R15.2, R17.2, U4.4 (DO)
unnamed: R16.2, U4.2 (SCLK), U5.62 (EECLK)
unnamed: R18.2, U5.6 (REF)
unnamed: R20.2, U5.14 (~RESET)
VBUS: C2.1, C24.1, J2.1 (VBUS), R5.1, R7.1, R13.1, U2.11 (~SHDN2), U2.13 (IN2), U2.14 (IN2), U2.17 (IN1), U2.18 (IN1), U2.20 (~SHDN1); also elsewhere on the board

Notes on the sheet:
JP1: Load EEPROM to CRAM
J1: Close 1,3 and 2,4 for programming Flash Close 3,4 and 1,2 for writing CRAM directly

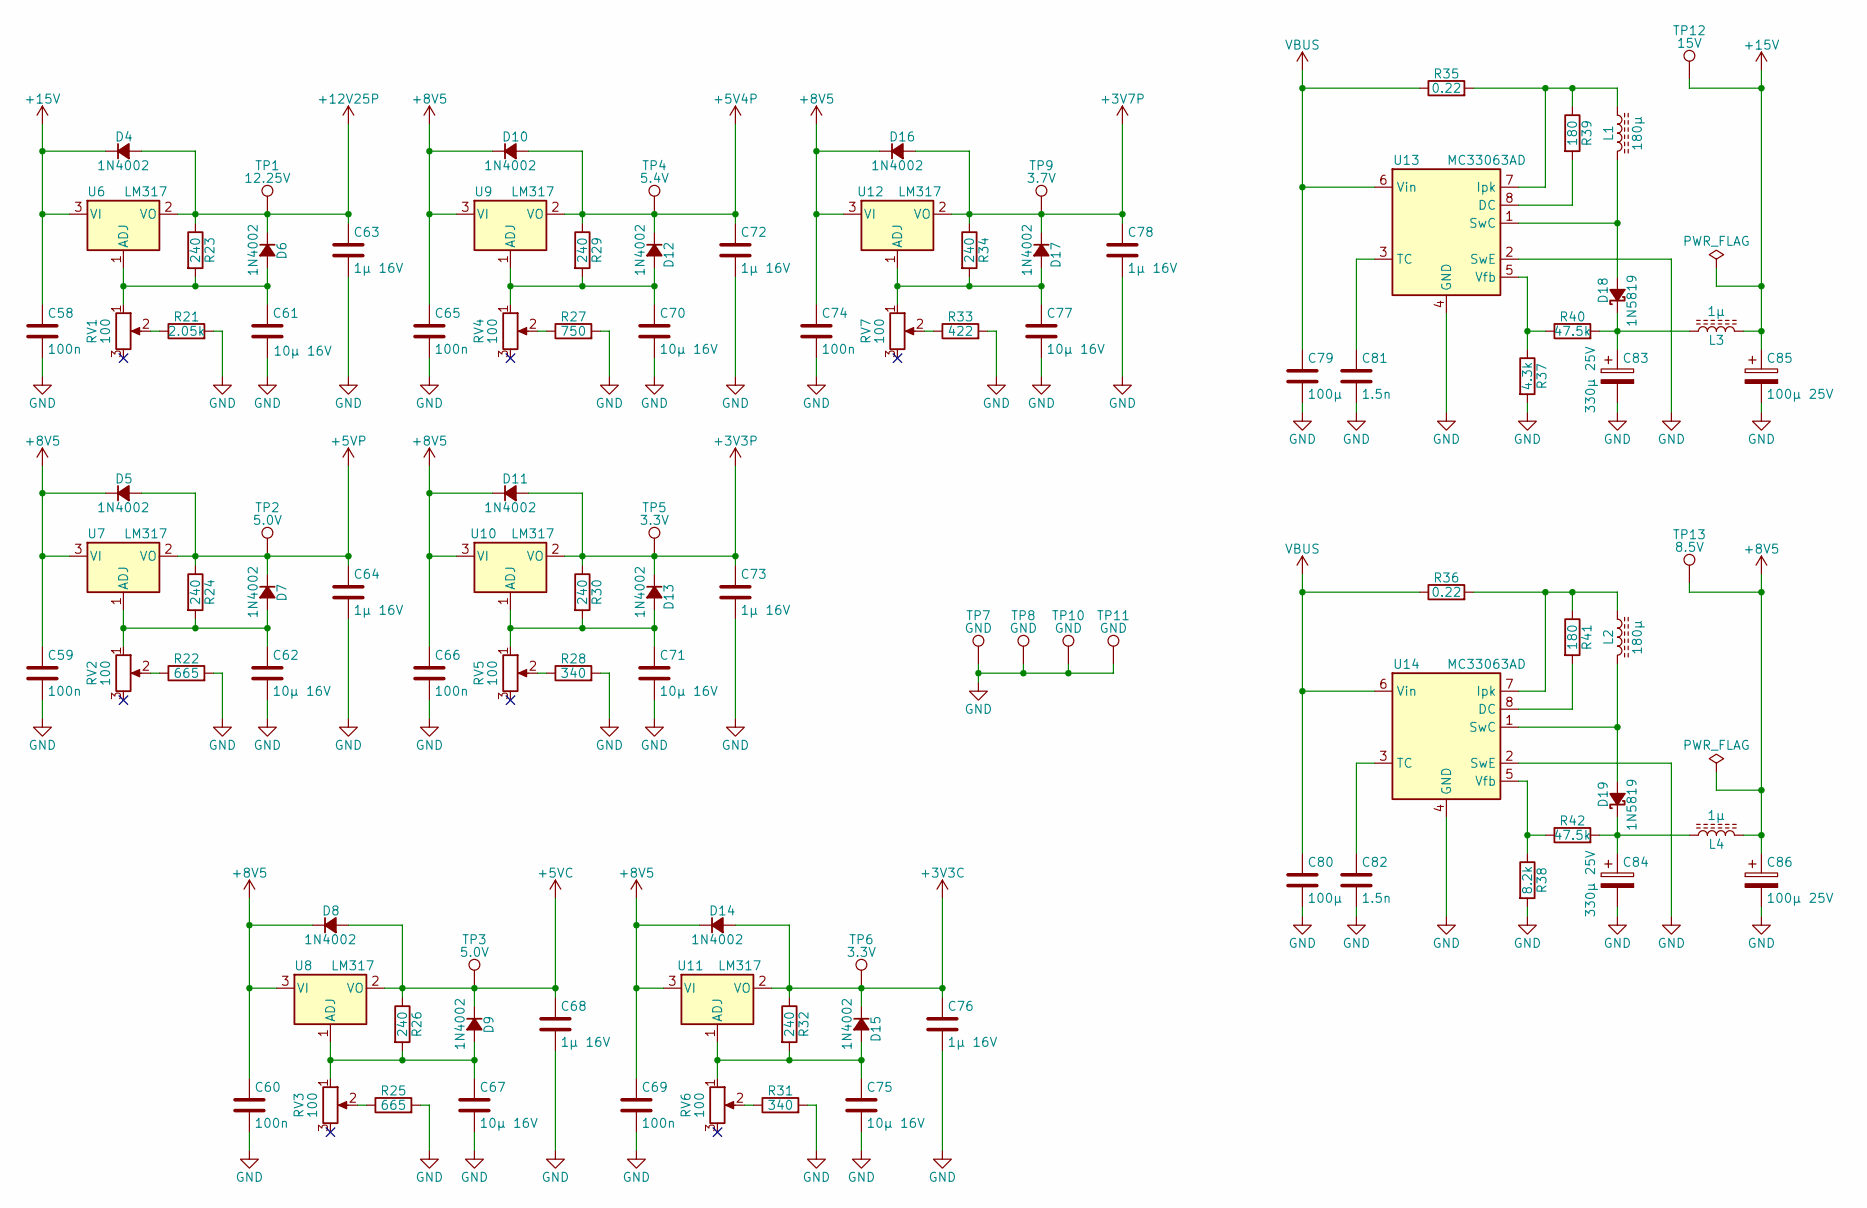
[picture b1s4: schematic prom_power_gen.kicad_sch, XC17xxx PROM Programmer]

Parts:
C58, C59, C60, C65, C66, C69, C74: 100n; C_0603_1608Metric
C61, C62, C67, C70, C71, C75, C77: 10µ 16V; C_1206_3216Metric
C63, C64, C68, C72, C73, C76, C78: 1µ 16V; C_0603_1608Metric
C79, C80: 100µ; C_1206_3216Metric
C81, C82: 1.5n; C_0603_1608Metric
C83, C84: 330µ 25V; CP_Elec_8x10.5
C85, C86: 100µ 25V; CP_Elec_6.3x7.7
D4, D5, D6, D7, D8, D9, D10, D11, D12, D13, D14, D15, D16, D17: 1N4002; D_MELF
D18, D19: 1N5819; D_SOD-123
L1, L2: 180µ; L_7.3x7.3_H4.5
L3, L4: 1µ; L_0805_2012Metric_Pad1.15x1.40mm_HandSolder
R21: 2.05k; R_0603_1608Metric
R22, R25: 665; R_0603_1608Metric
R23, R24, R26, R29, R30, R32, R34: 240; R_0603_1608Metric
R27: 750; R_0603_1608Metric
R28, R31: 340; R_0603_1608Metric
R33: 422; R_0603_1608Metric
R35, R36: 0.22; R_2512_6332Metric
R37: 4.3k; R_0603_1608Metric
R38: 8.2k; R_0603_1608Metric
R39, R41: 180; R_0603_1608Metric
R40, R42: 47.5k; R_0603_1608Metric
RV1, RV2, RV3, RV4, RV5, RV6, RV7: 100; Potentiometer_Bourns_3296W_Vertical
TP1: 12.25V; TestPoint_Keystone_5010-5014_Multipurpose
TP2, TP3: 5.0V; TestPoint_Keystone_5010-5014_Multipurpose
TP4: 5.4V; TestPoint_Keystone_5010-5014_Multipurpose
TP5, TP6: 3.3V; TestPoint_Keystone_5010-5014_Multipurpose
TP7, TP8, TP10, TP11: GND; TestPoint_Keystone_5010-5014_Multipurpose
TP9: 3.7V; TestPoint_Keystone_5010-5014_Multipurpose
TP12: 15V; TestPoint_Keystone_5010-5014_Multipurpose
TP13: 8.5V; TestPoint_Keystone_5010-5014_Multipurpose
U6, U7, U8, U9, U10, U11, U12: LM317; SOT-223-3_TabPin2
U13, U14: MC33063AD; SOIC-8_3.9x4.9mm_P1.27mm

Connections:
+3V3C: C76.1, D14.2 (A), D15.1 (K), R32.1, TP6.1, U11.2 (VO); also elsewhere on the board
+3V3P: C73.1, D11.2 (A), D13.1 (K), R30.1, TP5.1, U10.2 (VO); also elsewhere on the board
+3V7P: C78.1, D16.2 (A), D17.1 (K), R34.1, TP9.1, U12.2 (VO); also elsewhere on the board
+5V4P: C72.1, D10.2 (A), D12.1 (K), R29.1, TP4.1, U9.2 (VO); also elsewhere on the board
+5VC: C68.1, D8.2 (A), D9.1 (K), R26.1, TP3.1, U8.2 (VO); also elsewhere on the board
+5VP: C64.1, D5.2 (A), D7.1 (K), R24.1, TP2.1, U7.2 (VO); also elsewhere on the board
+8V5: C59.1, C60.1, C65.1, C66.1, C69.1, C74.1, C86.1, D5.1 (K), D8.1 (K), D10.1 (K), D11.1 (K), D14.1 (K), D16.1 (K), L4.2, TP13.1, U7.3 (VI), U8.3 (VI), U9.3 (VI), U10.3 (VI), U11.3 (VI), U12.3 (VI)
+12V25P: C63.1, D4.2 (A), D6.1 (K), R23.1, TP1.1, U6.2 (VO); also elsewhere on the board
+15V: C58.1, C85.1, D4.1 (K), L3.2, TP12.1, U6.3 (VI)
GND: C58.2, C59.2, C60.2, C61.2, C62.2, C63.2, C64.2, C65.2, C66.2, C67.2, C68.2, C69.2, C70.2, C71.2, C72.2, C73.2, C74.2, C75.2, C76.2, C77.2, C78.2, C79.2, C80.2, C81.2, C82.2, C83.2, C84.2, C85.2, C86.2, R21.2, R22.2, R25.2, R27.2, R28.2, R31.2, R33.2, R37.2, R38.2, TP7.1, TP8.1, TP10.1, TP11.1, U13.2 (SwE), U13.4 (GND), U14.2 (SwE), U14.4 (GND); also elsewhere on the board
unnamed: C61.1, D6.2 (A), R23.2, RV1.1, U6.1 (ADJ)
unnamed: C62.1, D7.2 (A), R24.2, RV2.1, U7.1 (ADJ)
unnamed: C67.1, D9.2 (A), R26.2, RV3.1, U8.1 (ADJ)
unnamed: C70.1, D12.2 (A), R29.2, RV4.1, U9.1 (ADJ)
unnamed: C71.1, D13.2 (A), R30.2, RV5.1, U10.1 (ADJ)
unnamed: C75.1, D15.2 (A), R32.2, RV6.1, U11.1 (ADJ)
unnamed: C77.1, D17.2 (A), R34.2, RV7.1, U12.1 (ADJ)
unnamed: D18.2 (A), L1.2, U13.1 (SwC)
unnamed: C83.1, D18.1 (K), L3.1, R40.2
unnamed: D19.2 (A), L2.2, U14.1 (SwC)
unnamed: C84.1, D19.1 (K), L4.1, R42.2
unnamed: R21.1, RV1.2
unnamed: R22.1, RV2.2
unnamed: R25.1, RV3.2
unnamed: R27.1, RV4.2
unnamed: R28.1, RV5.2
unnamed: R31.1, RV6.2
unnamed: R33.1, RV7.2
unnamed: R39.2, U13.8 (DC)
unnamed: L1.1, R35.2, R39.1, U13.7 (Ipk)
unnamed: C81.1, U13.3 (TC)
unnamed: R37.1, R40.1, U13.5 (Vfb)
unnamed: R41.2, U14.8 (DC)
unnamed: L2.1, R36.2, R41.1, U14.7 (Ipk)
unnamed: C82.1, U14.3 (TC)
unnamed: R38.1, R42.1, U14.5 (Vfb)
VBUS: C79.1, C80.1, R35.1, R36.1, U13.6 (Vin), U14.6 (Vin); also elsewhere on the board

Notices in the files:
pcb/xc17_prom_prog/fpga.kicad_sch:
CC-BY-SA-4.0 Michael Singer
